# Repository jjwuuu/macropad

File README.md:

## Bill of Materials
### Required
 - 1x Seeed Studio XIAO RP2040
 - 6x MX hotswap sockets
 - 7x 1N4148 small signal diodes
 - 1x EC11 rotary encoder with push button
 - 4x M3x12 screws (support M3x8 - M3x14) 
 
## Assembly Instructions 

1. 3D print the top case, bottom case, and knob. For the best results, print the top case and bottom case with 100% infill.
2. Solder the hotswap sockets and diodes, taking note of the polarity. 
3. Solder the microcontroller, using pin headers to align the pads but not soldering the pin headers.
4. Solder the rotary encoder on the opposite side of the board as the rest of the components.
5. Press and hold the BOOT button on the microcontroller. Then, while still holding the button, plug in the microcontroller to a computer. The microcontroller should appear as a virtual USB storage device.
6. Upload the .uf2 firmware file to the microcontroller. The virtual USB storage device should disconnect once flashed.
7. Unplug and replug the USB cable.
8. Test that the keys work by inserting switches into the hotswap sockets and depressing them. The keys should type the numbers 1-6 by default.
9. Test that the rotary encoder works by rotating it and pressing it. The encoder should control volume when rotated and type the number 7 when pressed.
10. Unplug the USB cable.
11. Insert the completed PCB into the bottom case, slotting in the USB conector first.
12. Place the top case on top of the bottom case.
13. Secure the bottom case to the top case with the M3x12 screws or the printable pegs/rivets.
14. Insert the switches into the top case. The switches should securely slot into the hotswap sockets.
15. Attach the keycaps and knob to the key switches and rotary encoder.
16. Connect the USB cable.
17. Open the [VIA app](https://www.usevia.app/).
18. Go to the "Settings" tab and enable "Show Design tab".
19. Go to the "Design" tab and upload the .json file.
20. Go to the "Configure" tab. After authorizing the device, the macropad is now configurable!

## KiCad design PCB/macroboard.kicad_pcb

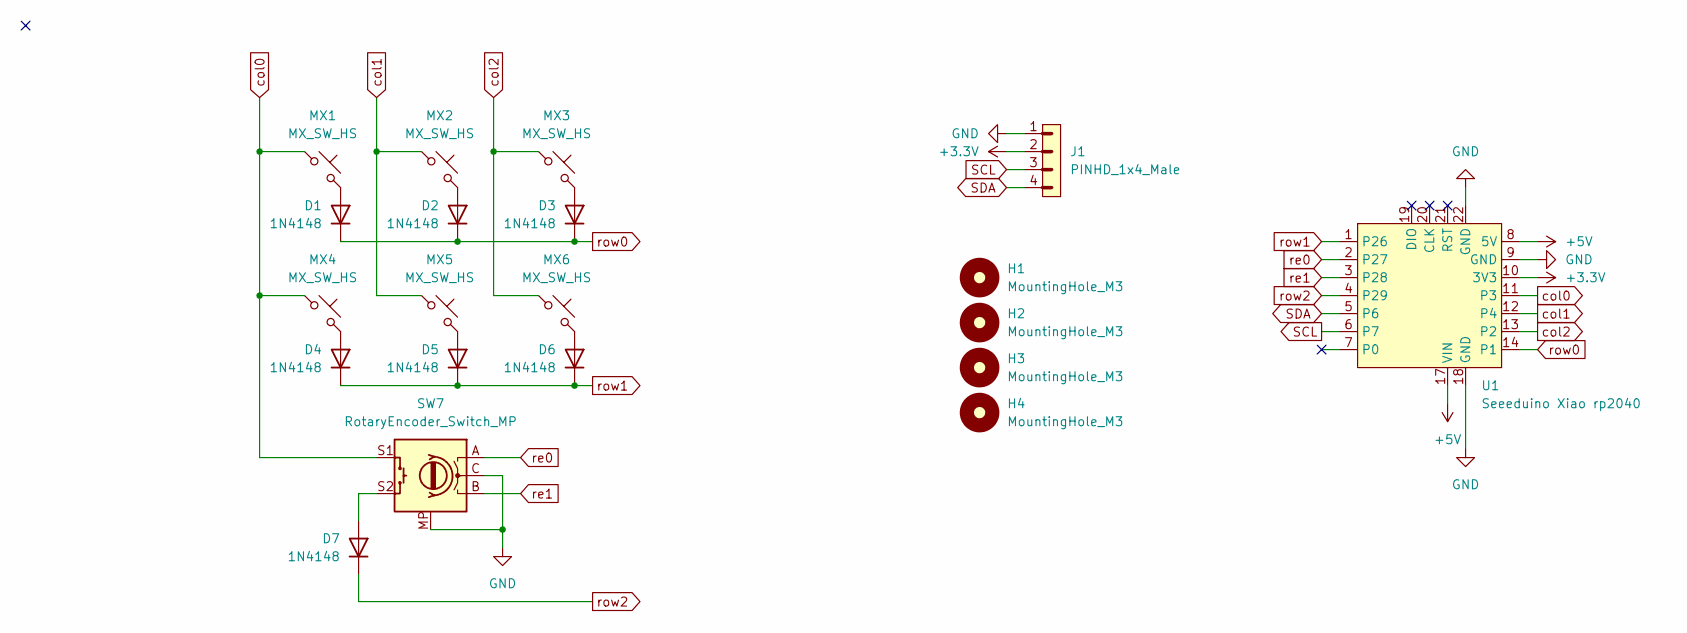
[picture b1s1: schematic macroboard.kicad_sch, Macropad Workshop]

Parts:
D1, D2, D3, D4, D5, D6, D7: 1N4148; D_DO-35_SOD27_P7.62mm_Horizontal_Hybrid
H1, H2, H3, H4: MountingHole_M3; MountingHole_3.2mm_M3_Pad
J1: PINHD_1x4_Male; PinHeader_1x04_P2.54mm_Horizontal
MX1, MX2, MX3, MX4, MX5, MX6: MX_SW_HS; SW_MX_HS_CPG151101S11_1u
SW7: RotaryEncoder_Switch_MP; ROT_Alps_EC11E-Switch
U1: Seeeduino Xiao rp2040; Xiao_rp2040_ACH

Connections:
+3.3V: J1.2, U1.10 (3V3)
+5V: U1.8 (5V), U1.17 (VIN)
GND: J1.1, SW7.C, SW7.MP, U1.9 (GND), U1.18 (GND), U1.22 (GND)
unnamed: D1.2 (A), MX1.2
unnamed: D2.2 (A), MX2.2
unnamed: D3.2 (A), MX3.2
unnamed: D4.2 (A), MX4.2
unnamed: D5.2 (A), MX5.2
unnamed: D6.2 (A), MX6.2
unnamed: D7.2 (A), SW7.S2
RGB: U1.7 (P0)
SCL: J1.3, U1.6 (P7)
SDA: J1.4, U1.5 (P6)
col0: MX1.1, MX4.1, SW7.S1, U1.11 (P3)
col1: MX2.1, MX5.1, U1.12 (P4)
col2: MX3.1, MX6.1, U1.13 (P2)
re0: SW7.A, U1.2 (P27)
re1: SW7.B, U1.3 (P28)
row0: D1.1 (K), D2.1 (K), D3.1 (K), U1.14 (P1)
row1: D4.1 (K), D5.1 (K), D6.1 (K), U1.1 (P26)
row2: D7.1 (K), U1.4 (P29)

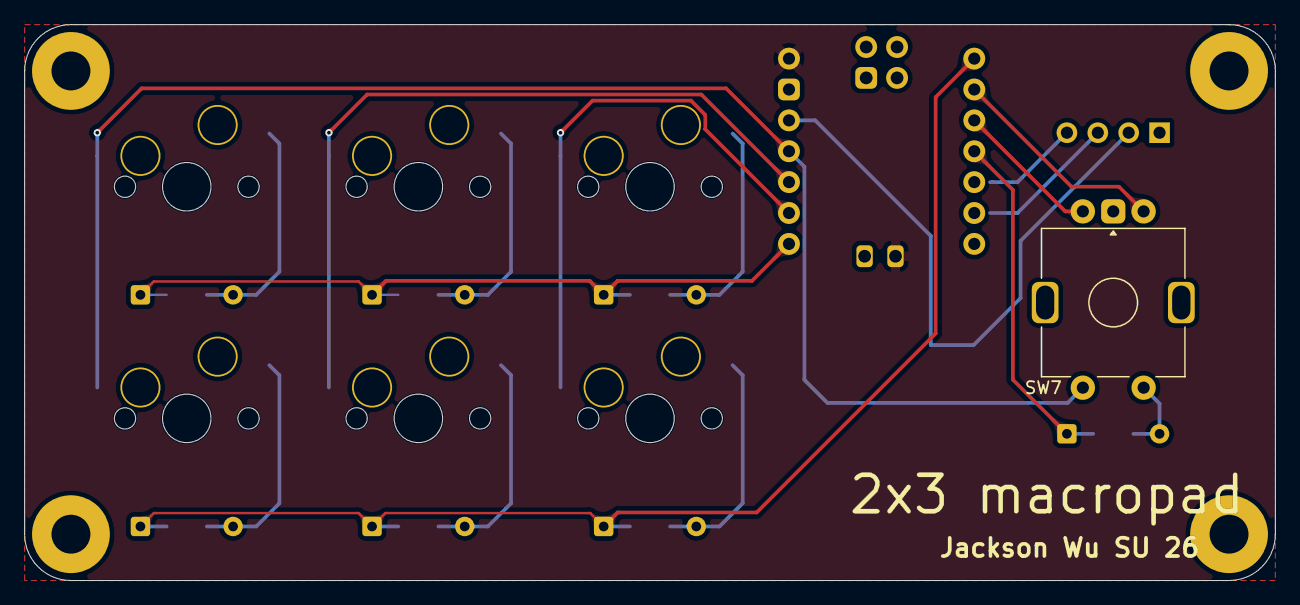
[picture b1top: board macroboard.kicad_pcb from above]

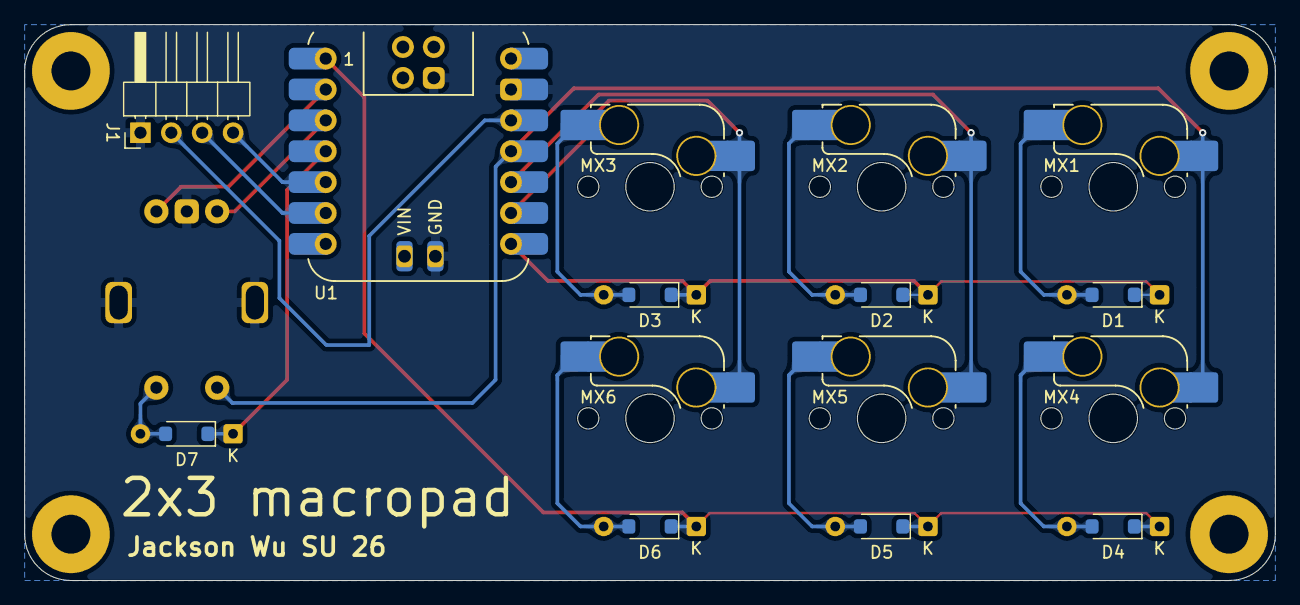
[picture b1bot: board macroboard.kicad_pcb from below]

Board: 2 copper layers, 102.9 x 45.7 mm, 20 parts (15 on the bottom side), 20 nets.

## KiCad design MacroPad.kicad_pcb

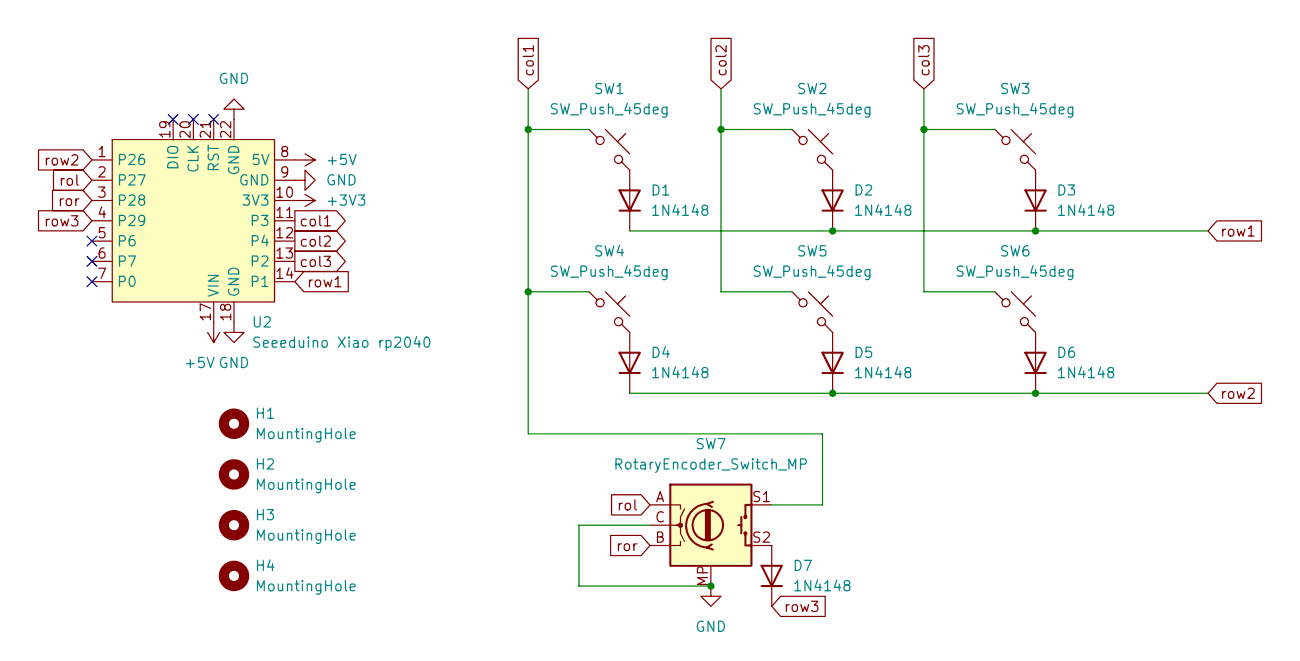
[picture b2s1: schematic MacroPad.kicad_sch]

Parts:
D1, D2, D3, D4, D5, D6, D7: 1N4148; D_DO-35_SOD27_P7.62mm_Horizontal
H1, H2, H3, H4: MountingHole; MountingHole_3.2mm_M3_Pad
SW1, SW2, SW3, SW4, SW5, SW6: SW_Push_45deg; SW_Cherry_MX_1.00u_PCB
SW7: RotaryEncoder_Switch_MP; ROT_Alps_EC11E-Switch
U2: Seeeduino Xiao rp2040; Xiao_rp2040_ACH

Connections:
+3V3: U2.10 (3V3)
+5V: U2.8 (5V), U2.17 (VIN)
GND: SW7.C, SW7.MP, U2.9 (GND), U2.18 (GND), U2.22 (GND)
unnamed: D1.2 (A), SW1.2
unnamed: D2.2 (A), SW2.2
unnamed: D3.2 (A), SW3.2
unnamed: D4.2 (A), SW4.2
unnamed: D5.2 (A), SW5.2
unnamed: D6.2 (A), SW6.2
unnamed: D7.2 (A), SW7.S2
col1: SW1.1, SW4.1, SW7.S1, U2.11 (P3)
col2: SW2.1, SW5.1, U2.12 (P4)
col3: SW3.1, SW6.1, U2.13 (P2)
rol: SW7.A, U2.2 (P27)
ror: SW7.B, U2.3 (P28)
row1: D1.1 (K), D2.1 (K), D3.1 (K), U2.14 (P1)
row2: D4.1 (K), D5.1 (K), D6.1 (K), U2.1 (P26)
row3: D7.1 (K), U2.4 (P29)

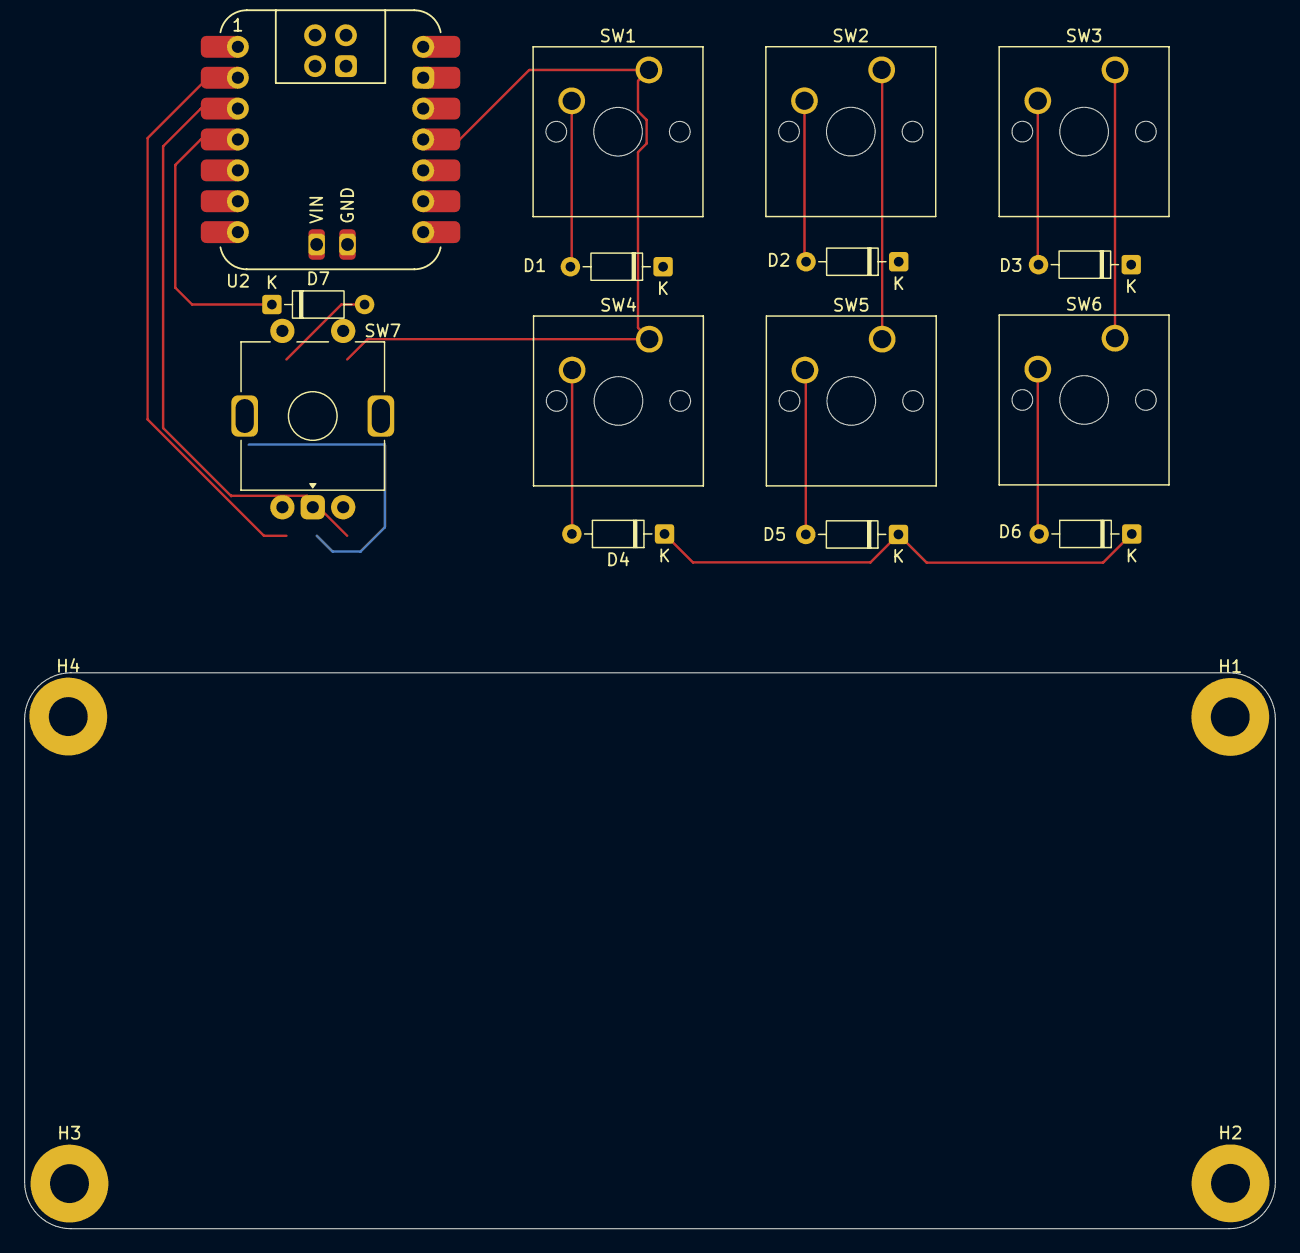
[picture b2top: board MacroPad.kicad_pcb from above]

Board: 2 copper layers, 102.9 x 45.7 mm, 19 parts (0 on the bottom side), 17 nets.
